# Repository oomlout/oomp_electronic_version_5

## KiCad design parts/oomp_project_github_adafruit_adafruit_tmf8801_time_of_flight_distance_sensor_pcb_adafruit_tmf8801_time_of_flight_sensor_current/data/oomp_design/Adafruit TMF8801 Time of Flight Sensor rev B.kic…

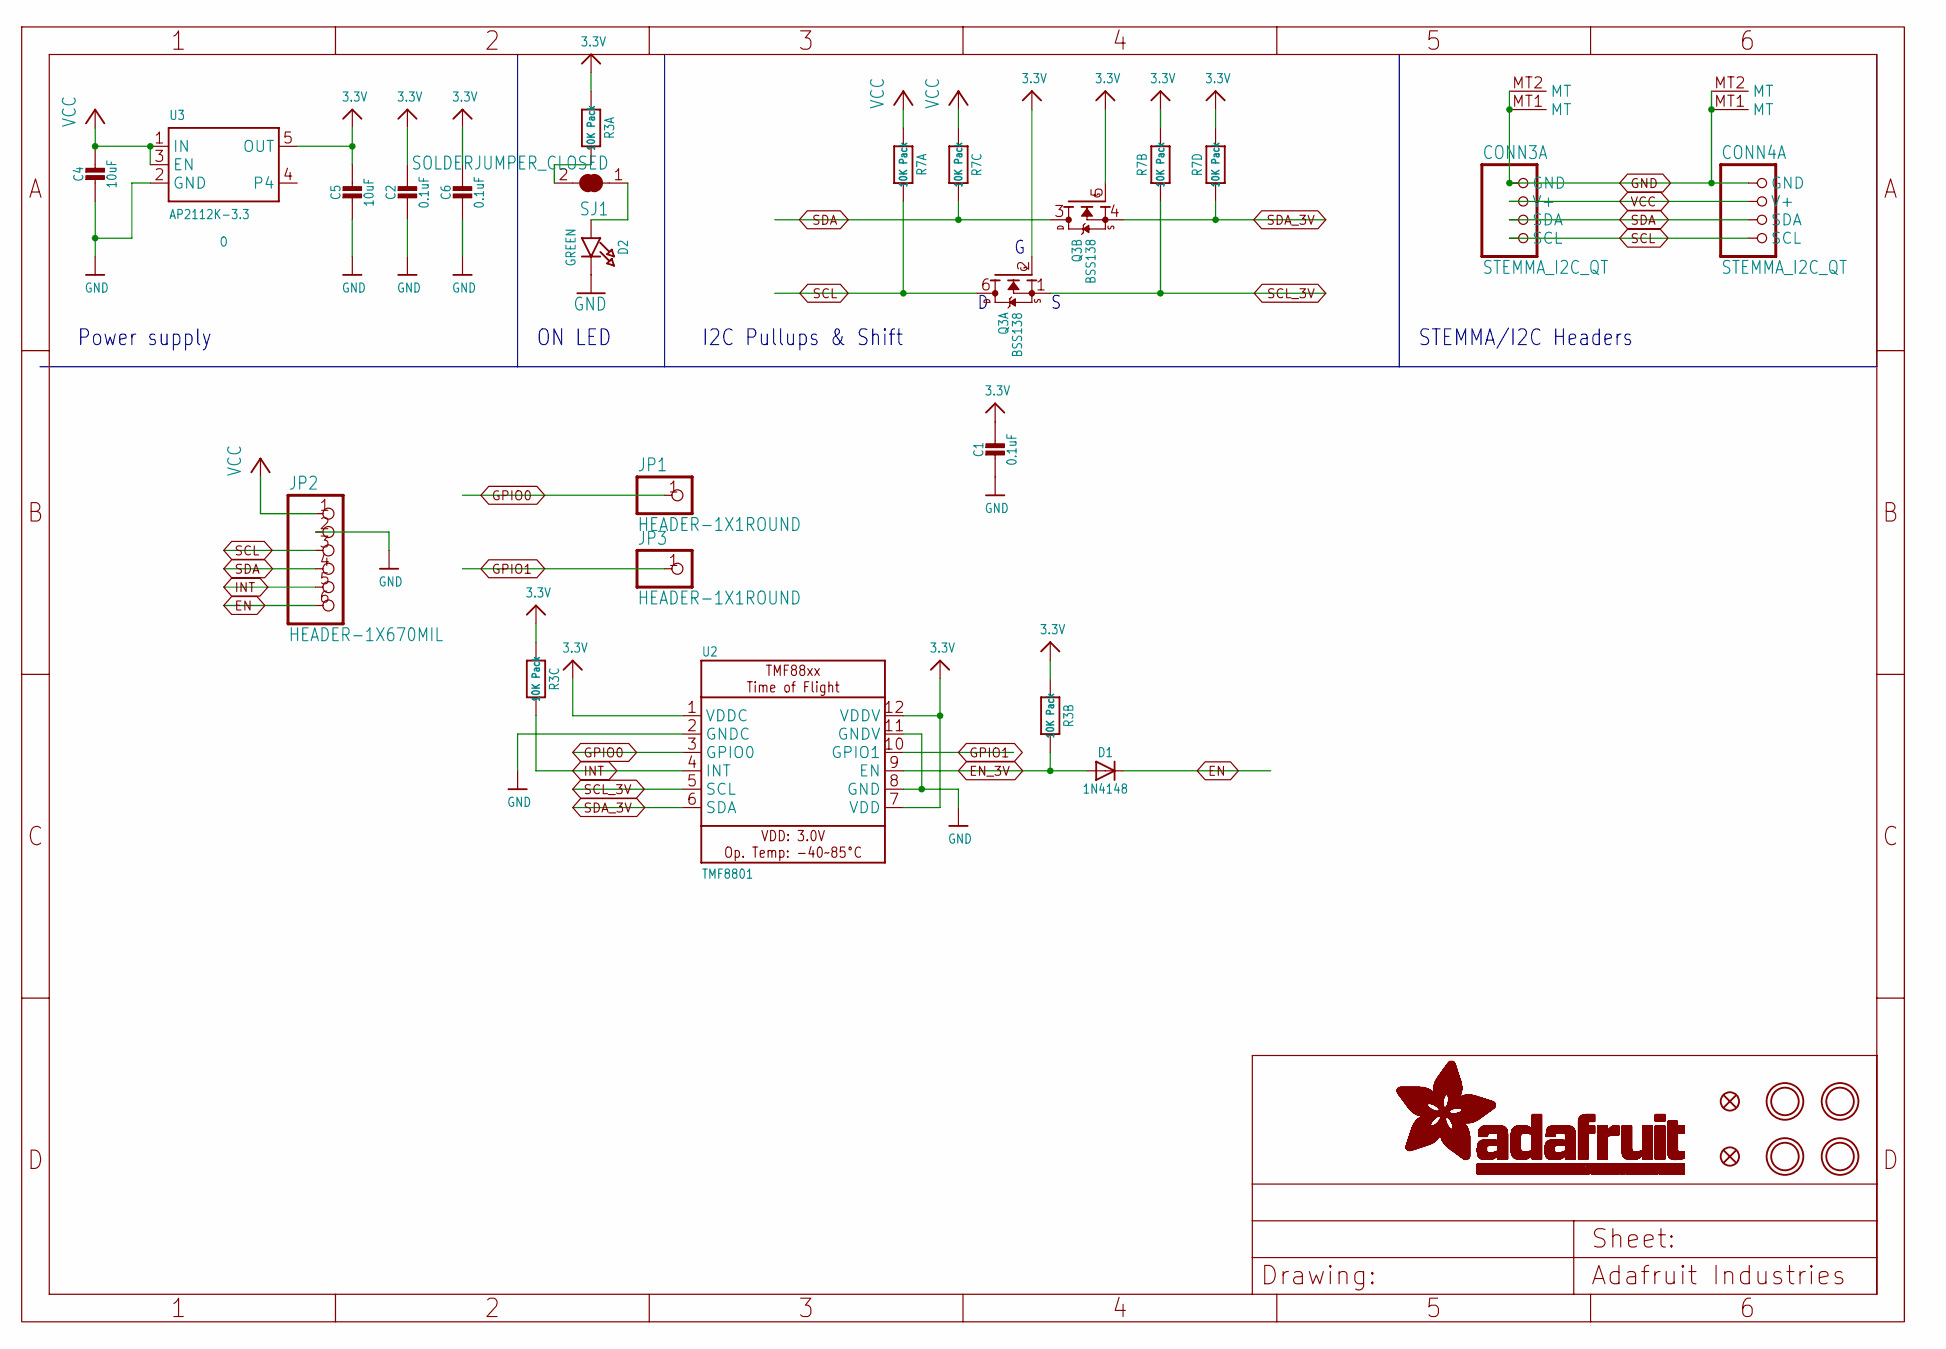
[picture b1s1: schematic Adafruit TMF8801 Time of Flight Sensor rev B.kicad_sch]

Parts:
C1, C2, C6: 0.1uF; 0603-NO
C4, C5: 10uF; 0805-NO
CONN3, CONN4: STEMMA_I2C_QT; JST_SH4; LCSC C2845363
D1: 1N4148; SOD-323
D2: GREEN; CHIPLED_0603_NOOUTLINE
FID1, FID4: FIDUCIAL_0.5MM
JP1, JP3: HEADER-1X1ROUND; 1X01_ROUND
JP2: HEADER-1X670MIL; 1X06_ROUND_70
Q3: BSS138; SOT363; JLC_ROTATION 270
R3, R7: 10K Pack; RESPACK_4X0603
SJ1: SOLDERJUMPER_CLOSED; SOLDERJUMPER_CLOSEDWIRE
U2: TMF8801; TMF880X
U3: AP2112K-3.3; SOT23-5; JLC_ROTATION 0
U$30, U$31, U$33, U$34: MOUNTINGHOLE2.5; MOUNTINGHOLE_2.5_PLATED

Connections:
3.3V: C1.1, C2.1, C5.1, C6.1, Q3.2 (G), Q3.5 (G), R3.1, R3.2 (1), R3.3 (1), R7.2 (1), R7.4 (1), U2.1 (VDDC), U2.7 (VDD), U2.12 (VDDV), U3.5 (OUT)
EN: D1.C, JP2.6
EN_3V: D1.A, R3.7 (2), U2.9 (EN)
GND: C1.2, C2.2, C4.2, C5.2, C6.2, CONN3.1 (GND), CONN3.MT1 (MT), CONN3.MT2 (MT), CONN4.1 (GND), CONN4.MT1 (MT), CONN4.MT2 (MT), D2.C, JP2.2, U2.2 (GNDC), U2.8 (GND), U2.11 (GNDV), U3.2 (GND)
GPIO0: JP1.1, U2.3 (GPIO0)
GPIO1: JP3.1, U2.10 (GPIO1)
INT: JP2.5, R3.6 (2), U2.4 (INT)
unnamed: R3.8 (2), SJ1.2
unnamed: D2.A, SJ1.1
SCL: CONN3.4 (SCL), CONN4.4 (SCL), JP2.3, Q3.6 (D), R7.8 (2)
SCL_3V: Q3.1 (S), R7.7 (2), U2.5 (SCL)
SDA: CONN3.3 (SDA), CONN4.3 (SDA), JP2.4, Q3.3 (D), R7.6 (2)
SDA_3V: Q3.4 (S), R7.5 (2), U2.6 (SDA)
VCC: C4.1, CONN3.2 (V+), CONN4.2 (V+), JP2.1, R7.1, R7.3 (1), U3.1 (IN), U3.3 (EN)

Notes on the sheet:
Power supply
STEMMA/I2C Headers
I2C Pullups & Shift
ON LED

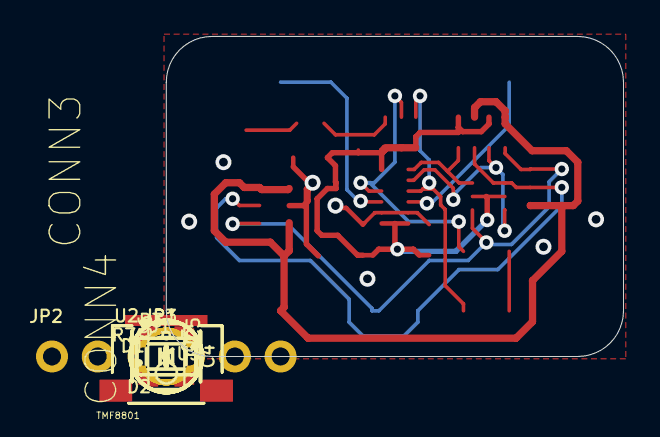
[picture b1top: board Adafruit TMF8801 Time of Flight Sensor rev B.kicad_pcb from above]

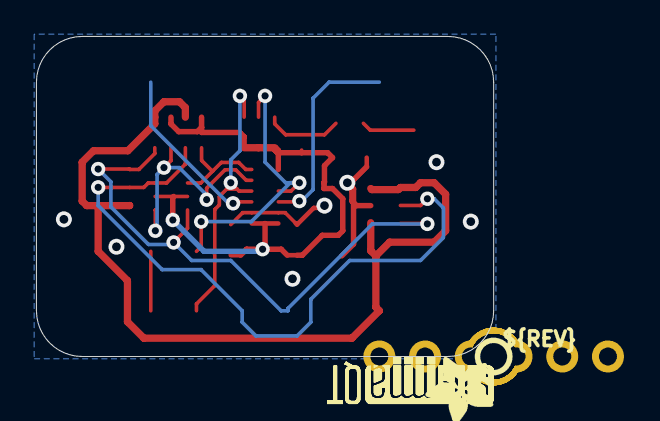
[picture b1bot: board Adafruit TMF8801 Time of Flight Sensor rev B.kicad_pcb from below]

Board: 2 copper layers, 25.4 x 17.8 mm, 43 parts (8 on the bottom side), 14 nets.

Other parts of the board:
PLABEL0: PLABEL0
PLABEL1: PLABEL1
PLABEL2: PLABEL2
PLABEL3: PLABEL3
PLABEL4: PLABEL4
PLABEL5: PLABEL5
PLABEL7: PLABEL7
PLABEL8: PLABEL8
PLABEL9: PLABEL9
PLABEL10: PLABEL10
PLABEL12: PLABEL12
PLABEL14: PLABEL14
PLABEL15: PLABEL15
PLABEL16: PLABEL16
PLABEL17: PLABEL17
U$36: ADAFRUIT_3.5MM
U$37: PCBFEAT-REV-040
U$38, U$39: STEMMAQT

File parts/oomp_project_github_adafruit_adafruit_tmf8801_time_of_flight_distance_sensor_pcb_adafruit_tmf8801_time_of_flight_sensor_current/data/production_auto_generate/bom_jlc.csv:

Comment,Designator,Footprint,LCSC Part #
,"JP1,JP3",Adafruit TMF8801 Time of Flight Sensor rev B-import-fps:1X01_ROUND,C7501259
,JP2,Adafruit TMF8801 Time of Flight Sensor rev B-import-fps:1X06_ROUND_70,C37208
,U$36,Adafruit TMF8801 Time of Flight Sensor rev B-import-fps:ADAFRUIT_3.5MM,
,U$37,Adafruit TMF8801 Time of Flight Sensor rev B-import-fps:PCBFEAT-REV-040,
,PLABEL0,Adafruit TMF8801 Time of Flight Sensor rev B-import-fps:PLABEL0,
,PLABEL1,Adafruit TMF8801 Time of Flight Sensor rev B-import-fps:PLABEL1,
,PLABEL10,Adafruit TMF8801 Time of Flight Sensor rev B-import-fps:PLABEL10,
,PLABEL12,Adafruit TMF8801 Time of Flight Sensor rev B-import-fps:PLABEL12,
,PLABEL14,Adafruit TMF8801 Time of Flight Sensor rev B-import-fps:PLABEL14,
,PLABEL15,Adafruit TMF8801 Time of Flight Sensor rev B-import-fps:PLABEL15,
,PLABEL16,Adafruit TMF8801 Time of Flight Sensor rev B-import-fps:PLABEL16,
,PLABEL17,Adafruit TMF8801 Time of Flight Sensor rev B-import-fps:PLABEL17,
,PLABEL2,Adafruit TMF8801 Time of Flight Sensor rev B-import-fps:PLABEL2,
,PLABEL3,Adafruit TMF8801 Time of Flight Sensor rev B-import-fps:PLABEL3,
,PLABEL4,Adafruit TMF8801 Time of Flight Sensor rev B-import-fps:PLABEL4,
,PLABEL5,Adafruit TMF8801 Time of Flight Sensor rev B-import-fps:PLABEL5,
,PLABEL7,Adafruit TMF8801 Time of Flight Sensor rev B-import-fps:PLABEL7,
,PLABEL8,Adafruit TMF8801 Time of Flight Sensor rev B-import-fps:PLABEL8,
,PLABEL9,Adafruit TMF8801 Time of Flight Sensor rev B-import-fps:PLABEL9,
,"U$38,U$39",Adafruit TMF8801 Time of Flight Sensor rev B-import-fps:STEMMAQT,
0.1uF,"C1,C2,C6",Adafruit TMF8801 Time of Flight Sensor rev B-import-fps:0603-NO,C14663
10K Pack,"R3,R7",Adafruit TMF8801 Time of Flight Sensor rev B-import-fps:RESPACK_4X0603,C98220
10uF,"C4,C5",Adafruit TMF8801 Time of Flight Sensor rev B-import-fps:0805-NO,
1N4148,D1,Adafruit TMF8801 Time of Flight Sensor rev B-import-fps:SOD-323,
AP2112K-3.3,U3,Adafruit TMF8801 Time of Flight Sensor rev B-import-fps:SOT23-5,
BSS138,Q3,Adafruit TMF8801 Time of Flight Sensor rev B-import-fps:SOT363,
GREEN,D2,Adafruit TMF8801 Time of Flight Sensor rev B-import-fps:CHIPLED_0603_NOOUTLINE,
STEMMA_I2C_QT,"CONN3,CONN4",Adafruit TMF8801 Time of Flight Sensor rev B-import-fps:JST_SH4,C160404
TMF8801,U2,Adafruit TMF8801 Time of Flight Sensor rev B-import-fps:TMF880X,

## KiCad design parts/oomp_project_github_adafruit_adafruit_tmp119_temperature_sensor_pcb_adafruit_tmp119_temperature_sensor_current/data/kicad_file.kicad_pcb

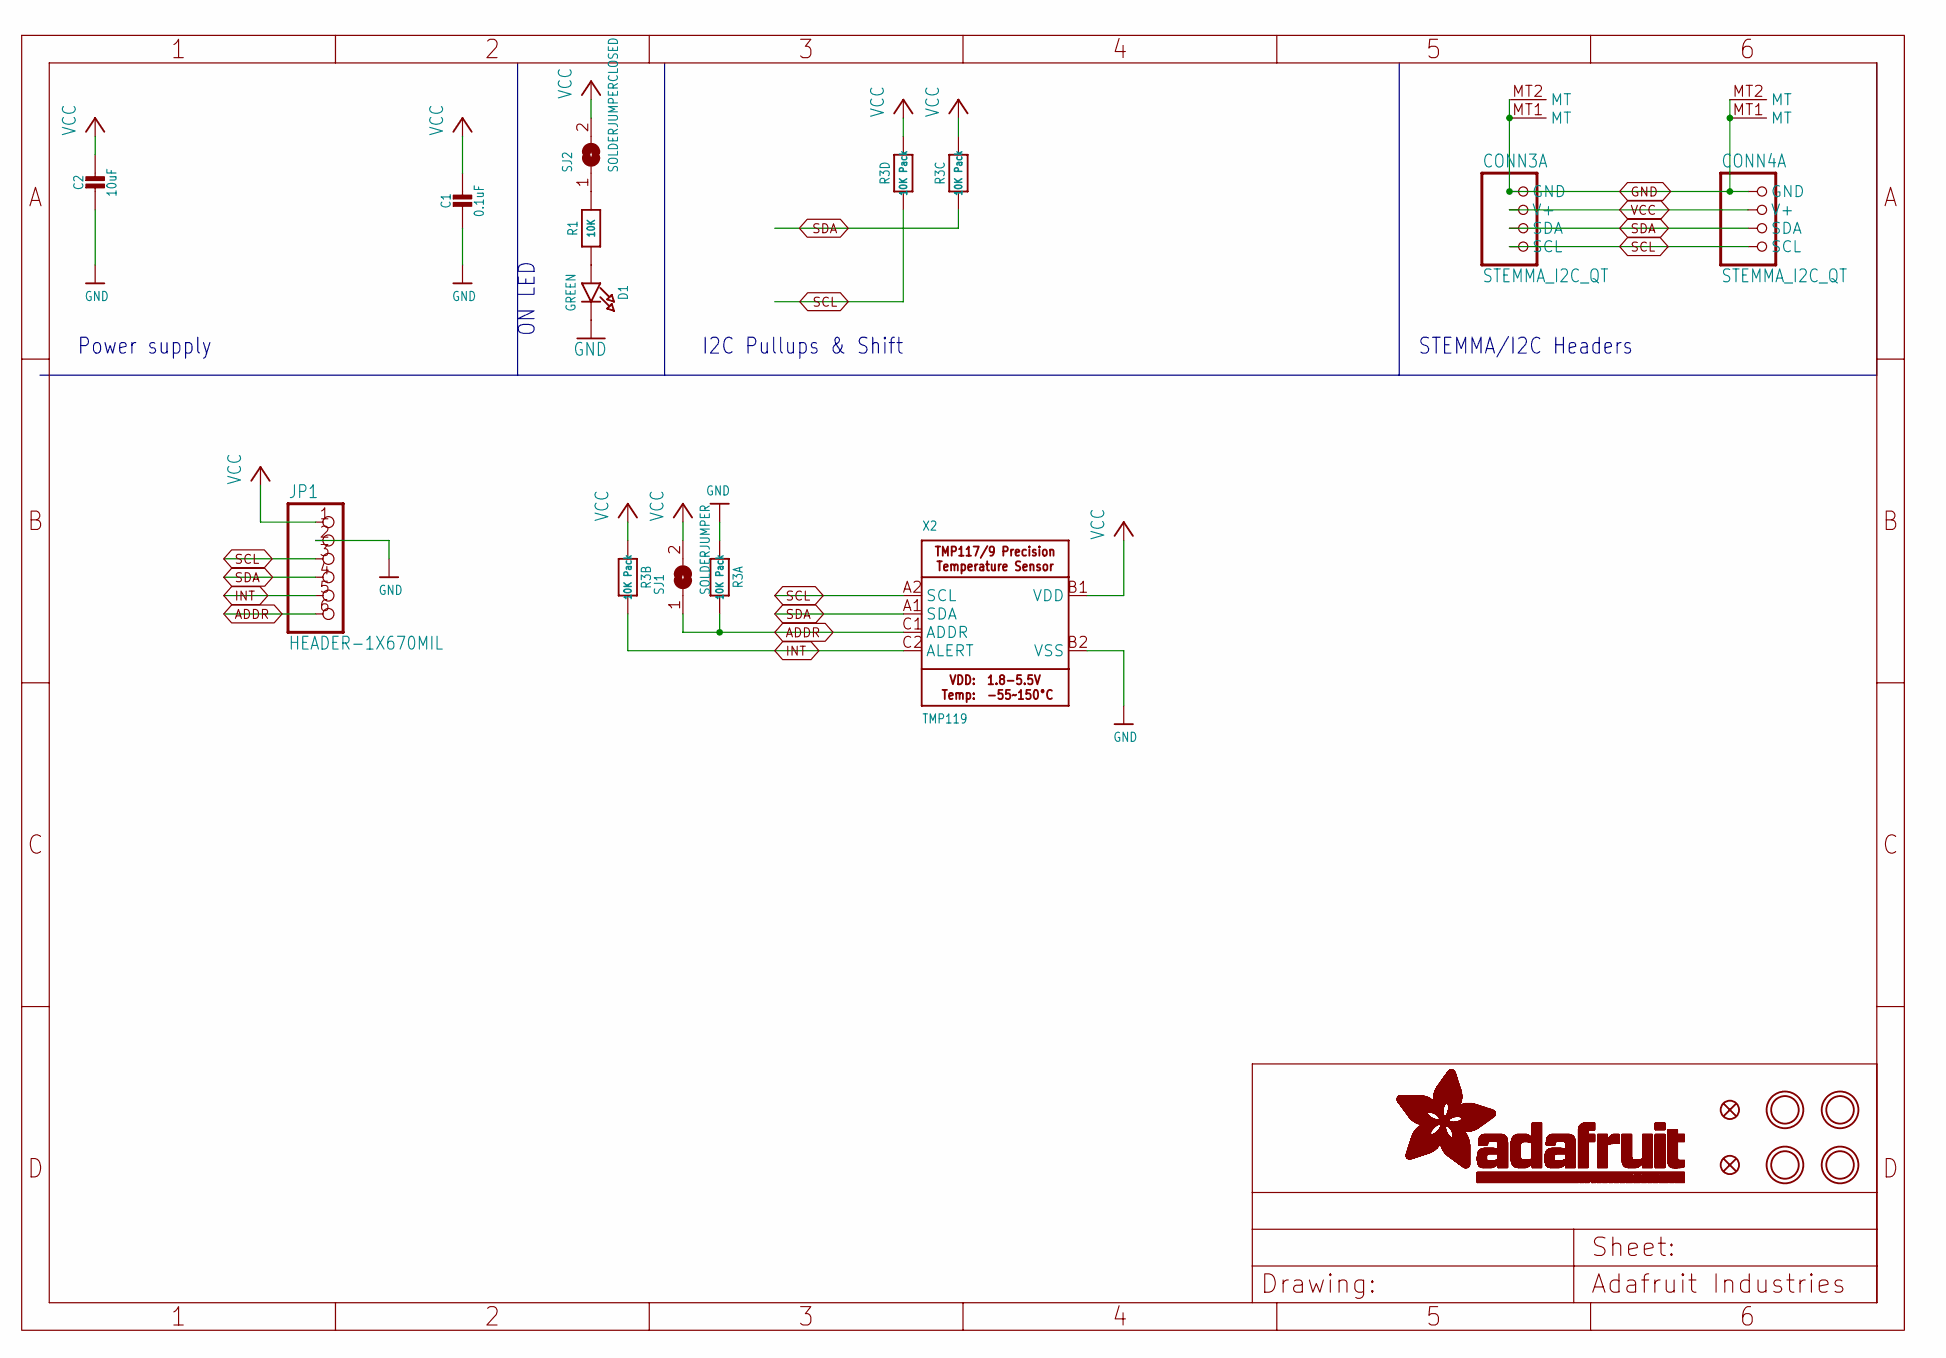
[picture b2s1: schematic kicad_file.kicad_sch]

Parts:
C1: 0.1uF; 0603-NO
C2: 10uF; 0805-NO
CONN3, CONN4: STEMMA_I2C_QT; JST_SH4; LCSC C2845363
D1: GREEN; CHIPLED_0603_NOOUTLINE
FID3, FID4: FIDUCIAL_0.5MM
JP1: HEADER-1X670MIL; 1X06_ROUND_70
R1: 10K; 0603-NO
R3: 10K Pack; RESPACK_4X0603
SJ1: SOLDERJUMPER; SOLDERJUMPER_ARROW_NOPASTE
SJ2: SOLDERJUMPERCLOSED; SOLDERJUMPER_CLOSEDWIRE
U$1, U$17, U$19, U$21: MOUNTINGHOLE2.5; MOUNTINGHOLE_2.5_PLATED
X2: TMP119; DSBGA-9

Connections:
ADDR: JP1.6, R3.8 (2), SJ1.1, X2.C1 (ADDR)
GND: C1.2, C2.2, CONN3.1 (GND), CONN3.MT1 (MT), CONN3.MT2 (MT), CONN4.1 (GND), CONN4.MT1 (MT), CONN4.MT2 (MT), D1.C, JP1.2, R3.1, X2.B2 (VSS)
INT: JP1.5, R3.7 (2), X2.C2 (ALERT)
unnamed: D1.A, R1.1
unnamed: R1.2, SJ2.1
SCL: CONN3.4 (SCL), CONN4.4 (SCL), JP1.3, R3.4 (1), X2.A2 (SCL)
SDA: CONN3.3 (SDA), CONN4.3 (SDA), JP1.4, R3.3 (1), X2.A1 (SDA)
VCC: C1.1, C2.1, CONN3.2 (V+), CONN4.2 (V+), JP1.1, R3.2 (1), R3.5 (2), R3.6 (2), SJ1.2, SJ2.2, X2.B1 (VDD)

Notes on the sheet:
ON LED
STEMMA/I2C Headers
I2C Pullups & Shift
Power supply

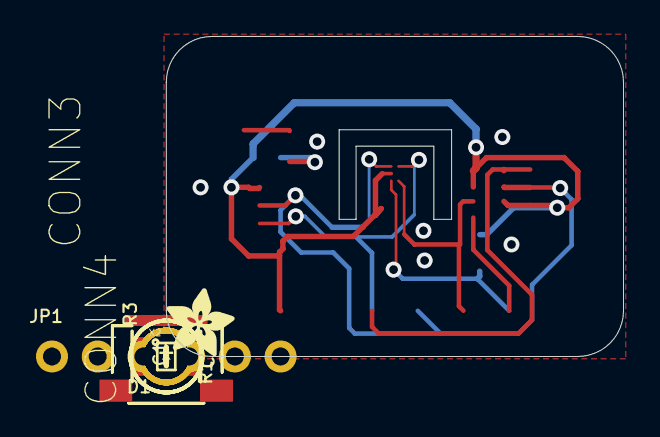
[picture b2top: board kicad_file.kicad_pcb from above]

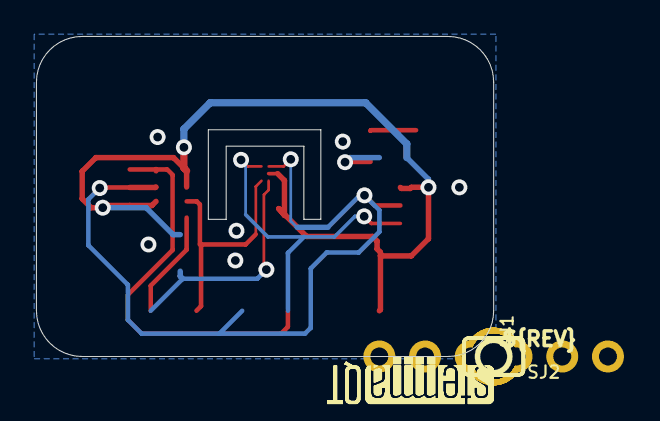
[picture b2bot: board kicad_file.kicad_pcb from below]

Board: 2 copper layers, 25.4 x 17.8 mm, 37 parts (12 on the bottom side), 8 nets.

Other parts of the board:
PLABEL0: PLABEL0
PLABEL1: PLABEL1
PLABEL2: PLABEL2
PLABEL3: PLABEL3
PLABEL4: PLABEL4
PLABEL5: PLABEL5
PLABEL6: PLABEL6
PLABEL7: PLABEL7
PLABEL8: PLABEL8
PLABEL9: PLABEL9
PLABEL10: PLABEL10
PLABEL11: PLABEL11
PLABEL12: PLABEL12
PLABEL13: PLABEL13
PLABEL14: PLABEL14
PLABEL15: PLABEL15
U$22: ADAFRUIT_3.5MM
U$25: PCBFEAT-REV-040
U$30, U$31: STEMMAQT

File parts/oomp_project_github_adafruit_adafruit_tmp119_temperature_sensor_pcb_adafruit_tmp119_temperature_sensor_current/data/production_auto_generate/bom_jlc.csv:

Comment,Designator,Footprint,LCSC Part #
,JP1,Adafruit TMP119 Temperature Sensor-import-fps:1X06_ROUND_70,C37208
,U$22,Adafruit TMP119 Temperature Sensor-import-fps:ADAFRUIT_3.5MM,
,U$25,Adafruit TMP119 Temperature Sensor-import-fps:PCBFEAT-REV-040,
,PLABEL0,Adafruit TMP119 Temperature Sensor-import-fps:PLABEL0,
,PLABEL1,Adafruit TMP119 Temperature Sensor-import-fps:PLABEL1,
,PLABEL10,Adafruit TMP119 Temperature Sensor-import-fps:PLABEL10,
,PLABEL11,Adafruit TMP119 Temperature Sensor-import-fps:PLABEL11,
,PLABEL12,Adafruit TMP119 Temperature Sensor-import-fps:PLABEL12,
,PLABEL13,Adafruit TMP119 Temperature Sensor-import-fps:PLABEL13,
,PLABEL14,Adafruit TMP119 Temperature Sensor-import-fps:PLABEL14,
,PLABEL15,Adafruit TMP119 Temperature Sensor-import-fps:PLABEL15,
,PLABEL2,Adafruit TMP119 Temperature Sensor-import-fps:PLABEL2,
,PLABEL3,Adafruit TMP119 Temperature Sensor-import-fps:PLABEL3,
,PLABEL4,Adafruit TMP119 Temperature Sensor-import-fps:PLABEL4,
,PLABEL5,Adafruit TMP119 Temperature Sensor-import-fps:PLABEL5,
,PLABEL6,Adafruit TMP119 Temperature Sensor-import-fps:PLABEL6,
,PLABEL7,Adafruit TMP119 Temperature Sensor-import-fps:PLABEL7,
,PLABEL8,Adafruit TMP119 Temperature Sensor-import-fps:PLABEL8,
,PLABEL9,Adafruit TMP119 Temperature Sensor-import-fps:PLABEL9,
,"U$30,U$31",Adafruit TMP119 Temperature Sensor-import-fps:STEMMAQT,
0.1uF,C1,Adafruit TMP119 Temperature Sensor-import-fps:0603-NO,C14663
10K,R1,Adafruit TMP119 Temperature Sensor-import-fps:0603-NO,C98220
10K Pack,R3,Adafruit TMP119 Temperature Sensor-import-fps:RESPACK_4X0603,C98220
10uF,C2,Adafruit TMP119 Temperature Sensor-import-fps:0805-NO,
GREEN,D1,Adafruit TMP119 Temperature Sensor-import-fps:CHIPLED_0603_NOOUTLINE,
STEMMA_I2C_QT,"CONN3,CONN4",Adafruit TMP119 Temperature Sensor-import-fps:JST_SH4,C160404
TMP119,X2,Adafruit TMP119 Temperature Sensor-import-fps:DSBGA-9,

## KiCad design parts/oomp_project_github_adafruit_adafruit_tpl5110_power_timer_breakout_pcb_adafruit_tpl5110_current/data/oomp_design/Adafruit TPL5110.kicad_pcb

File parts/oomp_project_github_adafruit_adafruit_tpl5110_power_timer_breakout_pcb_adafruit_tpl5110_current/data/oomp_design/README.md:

# OOMP KiCad design copy

Open `Adafruit TPL5110.kicad_pro` (or the `.kicad_pcb` / `.kicad_sch`) in KiCad. Local OOMP libraries are under `libraries/`. Original inputs are preserved in [../original/](../original/).

Only verified unchanged installed KiCad defaults were renamed. Modified, custom, unmatched and unavailable items remain unchanged. Soldering variants are never swapped during conversion. Existing pad coordinates, nets and UUIDs are preserved.

See [conversion_report.yaml](conversion_report.yaml) for every conversion and skip. Copy this directory before editing; regeneration refuses to overwrite edited design files.

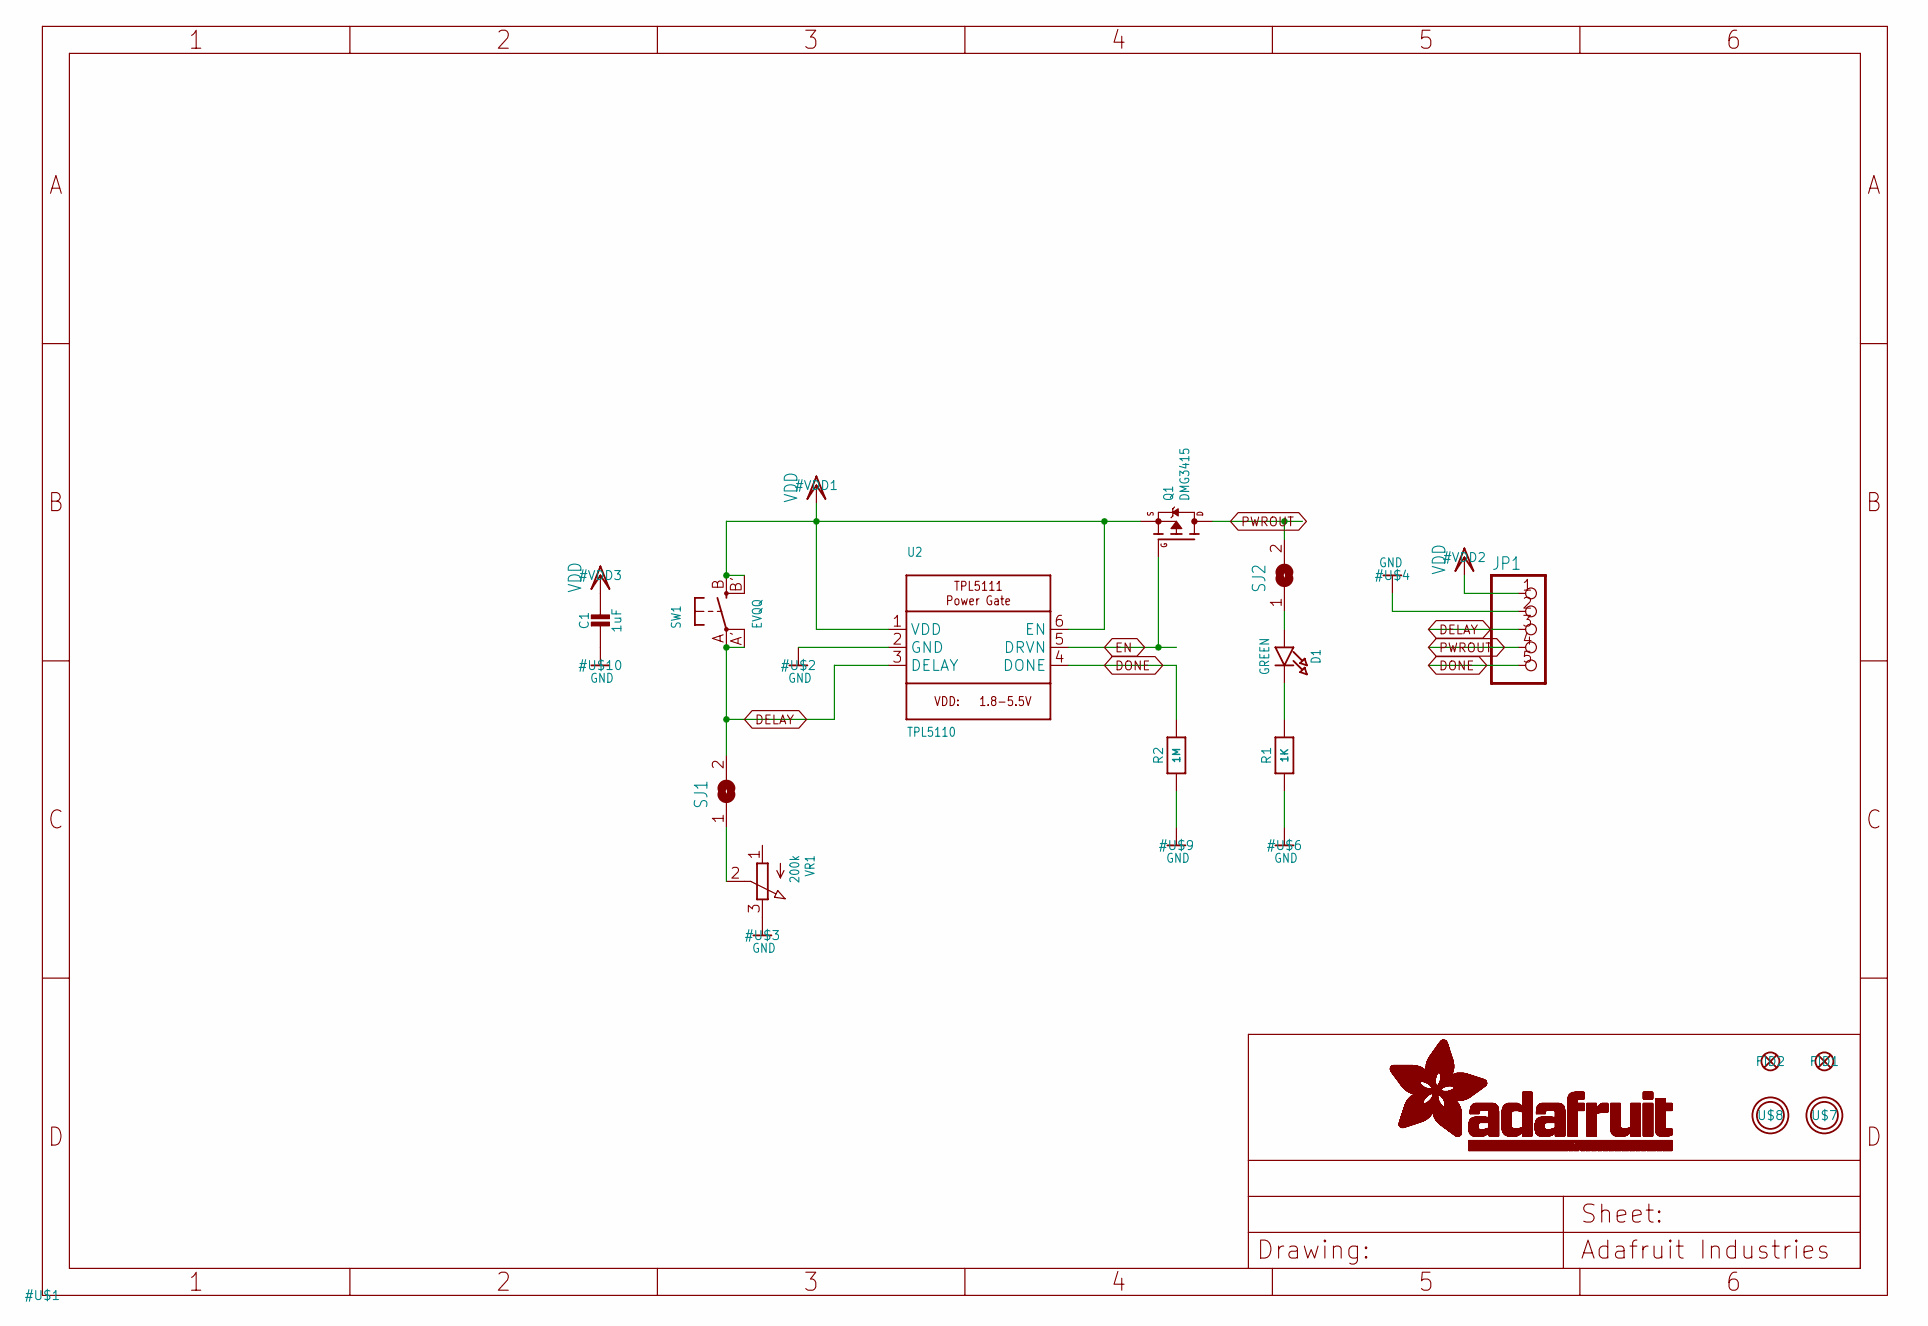
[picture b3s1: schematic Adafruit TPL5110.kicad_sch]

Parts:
C1: 1uF; 0805-NO
D1: GREEN; CHIPLED_0805_NOOUTLINE
FID1, FID2: FIDUCIAL""; FIDUCIAL_1MM
JP1: HEADER-1X570MIL; 1X05_ROUND_70
Q1: DMG3415; SOT23-WIDE
R1: 1K; 0805-NO
R2: 1M; 0805-NO
SJ1, SJ2: SOLDERJUMPERCLOSED; SOLDERJUMPER_CLOSEDWIRE
SW1: EVQQ; EVQ-Q2_SMALLER
U2: TPL5110; SOT23-6
U$7, U$8: MOUNTINGHOLE2.5; MOUNTINGHOLE_2.5_PLATED
VR1: 200k; TRIMPOT_BOURNS_TC33X-2

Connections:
DELAY: JP1.3, SJ1.2, SW1.A, SW1.A' (P1), U2.3 (DELAY)
DONE: JP1.5, R2.2, U2.4 (DONE)
EN: Q1.1 (G), U2.5 (DRVN)
GND: C1.2, JP1.2, R1.1, R2.1, U2.2 (GND), VR1.3 (E)
unnamed: SJ1.1, VR1.2 (S)
unnamed: D1.A, SJ2.1
unnamed: D1.C, R1.2
PWROUT: JP1.4, Q1.3 (D), SJ2.2
VDD: C1.1, JP1.1, Q1.2 (S), SW1.B (S), SW1.B' (S1), U2.1 (VDD), U2.6 (EN)

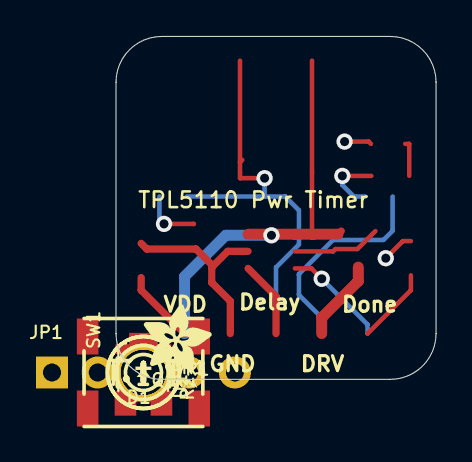
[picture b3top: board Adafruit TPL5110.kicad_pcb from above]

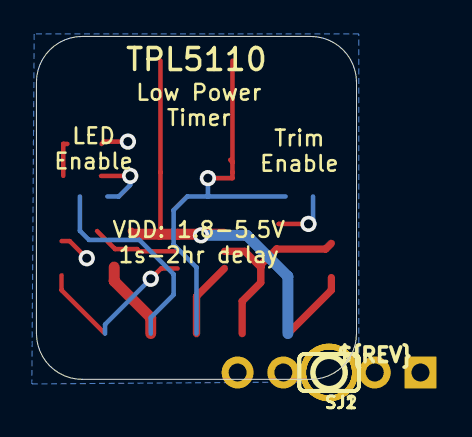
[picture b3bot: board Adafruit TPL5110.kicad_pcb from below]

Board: 2 copper layers, 17.8 x 19.1 mm, 17 parts (3 on the bottom side), 9 nets.

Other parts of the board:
U$5: ADAFRUIT_3.5MM
U$11: PCBFEAT-REV-040

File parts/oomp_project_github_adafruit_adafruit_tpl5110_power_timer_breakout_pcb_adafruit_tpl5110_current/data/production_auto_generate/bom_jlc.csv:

Comment,Designator,Footprint,LCSC Part #
,JP1,Adafruit TPL5110-import-fps:1X05_ROUND_70,C42431835
,U$5,Adafruit TPL5110-import-fps:ADAFRUIT_3.5MM,
,U$11,Adafruit TPL5110-import-fps:PCBFEAT-REV-040,
1K,R1,Adafruit TPL5110-import-fps:0805-NO,C17513
1M,R2,Adafruit TPL5110-import-fps:0805-NO,C2933280
1uF,C1,Adafruit TPL5110-import-fps:0805-NO,
200k,VR1,Adafruit TPL5110-import-fps:TRIMPOT_BOURNS_TC33X-2,
DMG3415,Q1,Adafruit TPL5110-import-fps:SOT23-WIDE,
EVQQ,SW1,Adafruit TPL5110-import-fps:EVQ-Q2_SMALLER,
GREEN,D1,Adafruit TPL5110-import-fps:CHIPLED_0805_NOOUTLINE,
TPL5110,U2,Adafruit TPL5110-import-fps:SOT23-6,

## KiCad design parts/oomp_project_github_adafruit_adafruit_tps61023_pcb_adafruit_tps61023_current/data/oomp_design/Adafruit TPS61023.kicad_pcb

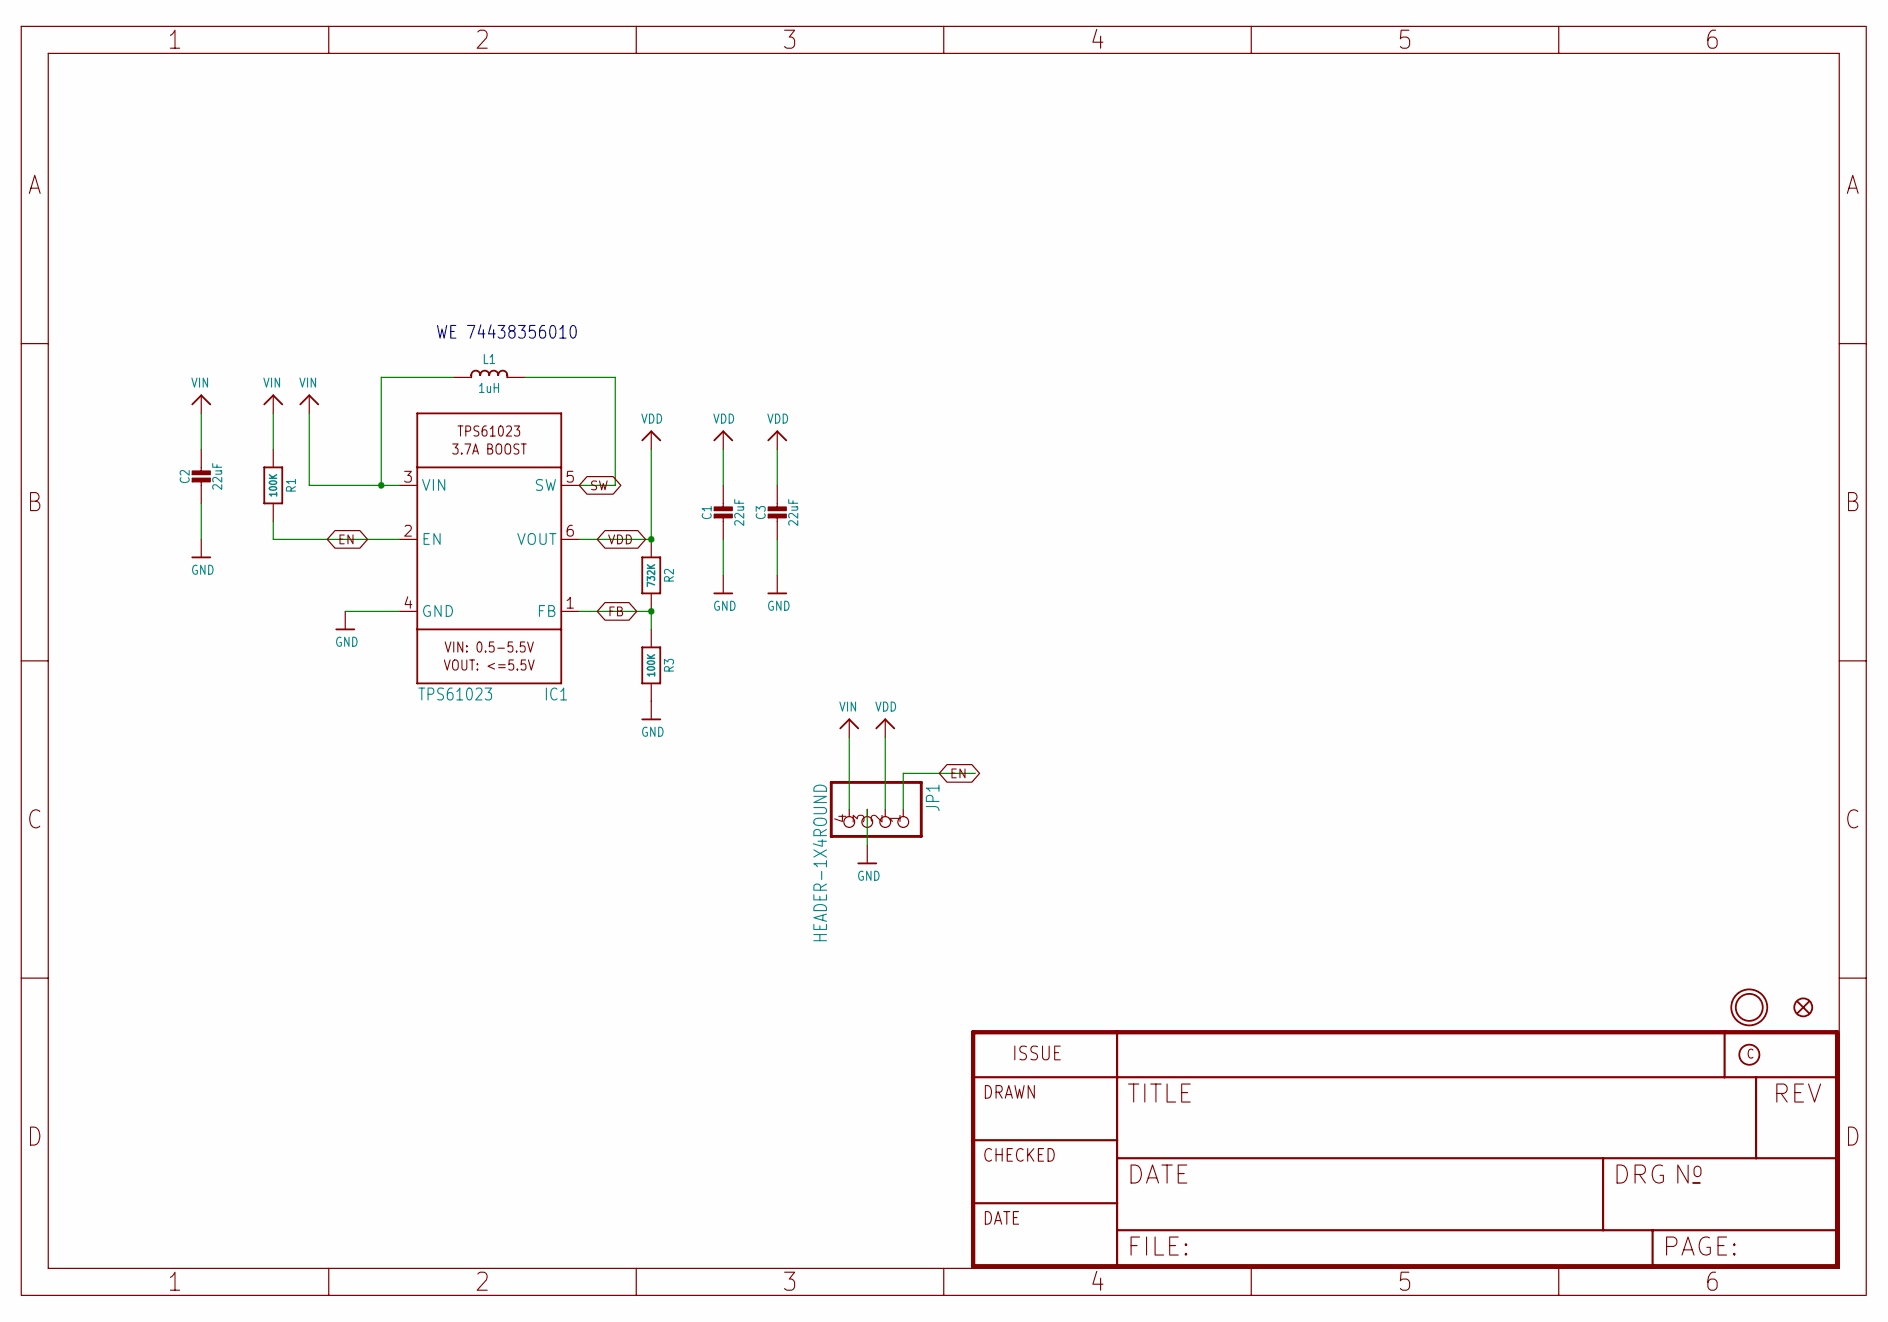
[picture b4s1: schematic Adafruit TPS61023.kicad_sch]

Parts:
C1, C2, C3: 22uF; 0805-NO
FID1: FIDUCIAL_1MM
IC1: TPS61023; SOT563
JP1: HEADER-1X4ROUND; 1X04_ROUND
L1: 1uH; INDUCTOR_5X5MM_TDK_VLC5045
R1, R3: 100K; 0603-NO
R2: 732K; 0603-NO
U$9: MOUNTINGHOLE2.5; MOUNTINGHOLE_2.5_PLATED

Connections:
EN: IC1.2 (EN), JP1.1, R1.2
FB: IC1.1 (FB), R2.2, R3.1
GND: C1.2, C2.2, C3.2, IC1.4 (GND), JP1.3, R3.2
SW: IC1.5 (SW), L1.P$2 (2)
VDD: C1.1, C3.1, IC1.6 (VOUT), JP1.2, R2.1
VIN: C2.1, IC1.3 (VIN), JP1.4, L1.P$1 (1), R1.1

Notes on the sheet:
WE 74438356010

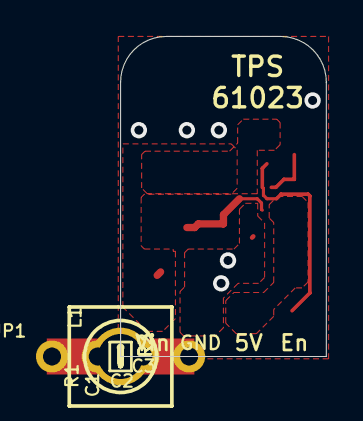
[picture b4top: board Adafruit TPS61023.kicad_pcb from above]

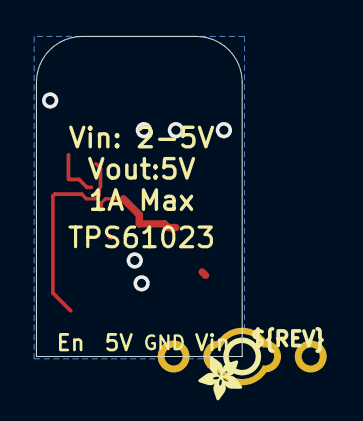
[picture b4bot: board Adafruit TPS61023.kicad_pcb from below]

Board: 2 copper layers, 11.4 x 17.8 mm, 13 parts (2 on the bottom side), 6 nets.

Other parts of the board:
U$10: PCBFEAT-REV-040
U$11: ADAFRUIT_2.5MM

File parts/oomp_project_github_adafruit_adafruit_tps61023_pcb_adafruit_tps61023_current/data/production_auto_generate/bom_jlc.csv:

Comment,Designator,Footprint,LCSC Part #
,JP1,Adafruit TPS61023-import-fps:1X04_ROUND,C42431795
,U$11,Adafruit TPS61023-import-fps:ADAFRUIT_2.5MM,
,U$10,Adafruit TPS61023-import-fps:PCBFEAT-REV-040,
100K,"R1,R3",Adafruit TPS61023-import-fps:0603-NO,C25803
1uH,L1,Adafruit TPS61023-import-fps:INDUCTOR_5X5MM_TDK_VLC5045,
22uF,"C1,C2,C3",Adafruit TPS61023-import-fps:0805-NO,
732K,R2,Adafruit TPS61023-import-fps:0603-NO,
TPS61023,IC1,Adafruit TPS61023-import-fps:SOT563,
